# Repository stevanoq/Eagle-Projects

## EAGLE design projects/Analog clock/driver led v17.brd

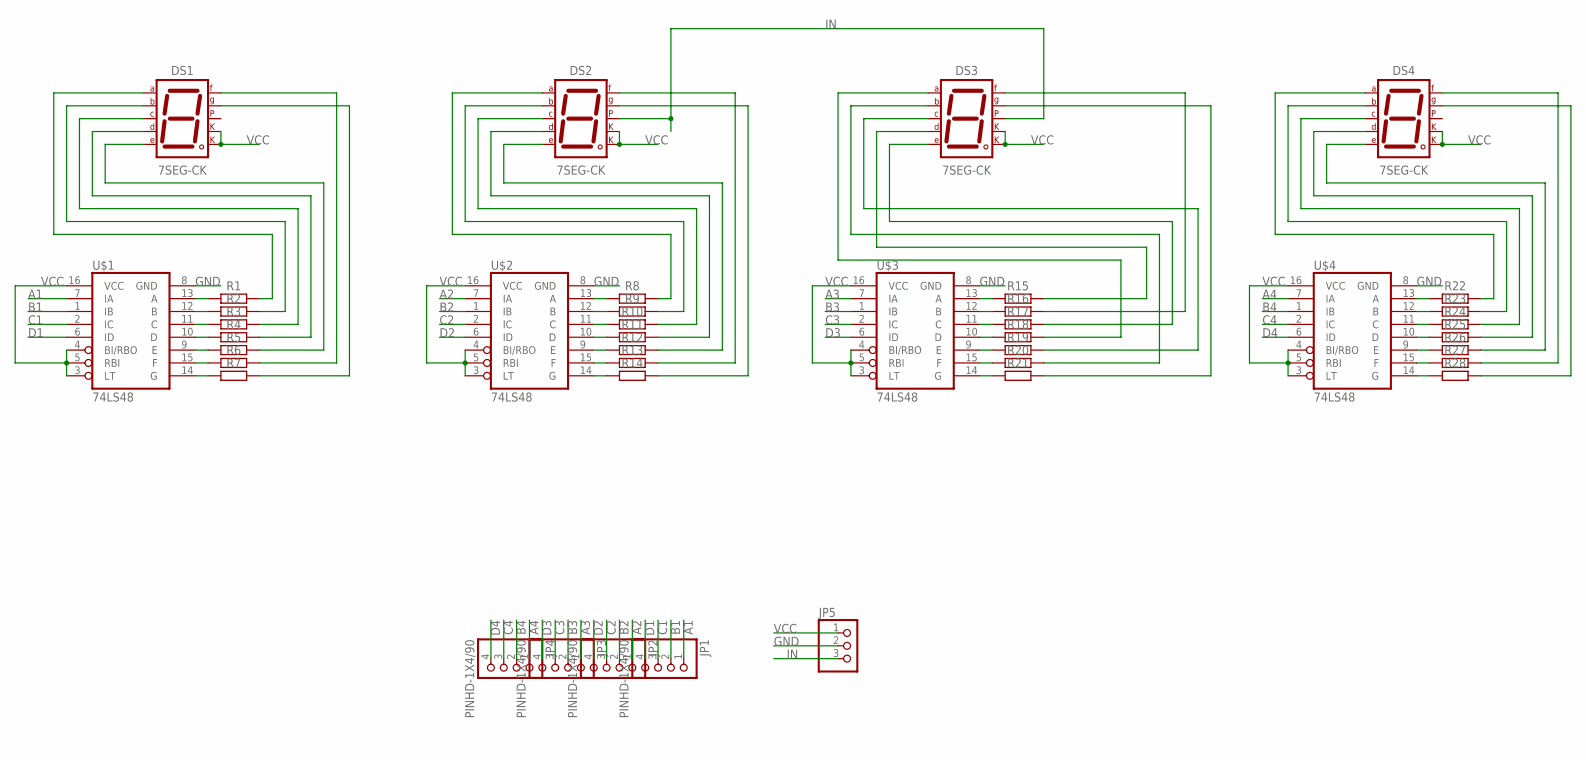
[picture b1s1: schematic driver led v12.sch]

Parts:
DS1, DS2, DS3, DS4: 7SEG-CK; 7SEG-13
JP1, JP2, JP3, JP4: PINHD-1X4/90; 1X04/90
JP5: PINHD-1X3CB; 1X03-CLEANBIG
R1, R2, R3, R4, R5, R6, R7, R8, R9, R10, R11, R12, R13, R14, R15, R16, R17, R18, R19, R20, R21, R22, R23, R24, R25, R26, R27, R28: R_AXIAL-7.2MM-PITCH; RESAD724W46L381D178B
U$1, U$2, U$3, U$4: 74LS48; DIO16

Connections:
A1: JP1.1, U$1.7 (IA)
A2: JP2.1, U$2.7 (IA)
A3: JP3.1, U$3.7 (IA)
A4: JP4.1, U$4.7 (IA)
B1: JP1.2, U$1.1 (IB)
B2: JP2.2, U$2.1 (IB)
B3: JP3.2, U$3.1 (IB)
B4: JP4.2, U$4.1 (IB)
C1: JP1.3, U$1.2 (IC)
C2: JP2.3, U$2.2 (IC)
C3: JP3.3, U$3.2 (IC)
C4: JP4.3, U$4.2 (IC)
D1: JP1.4, U$1.6 (ID)
D2: JP2.4, U$2.6 (ID)
D3: JP3.4, U$3.6 (ID)
D4: JP4.4, U$4.6 (ID)
GND: JP5.2, U$1.8 (GND), U$2.8 (GND), U$3.8 (GND), U$4.8 (GND)
IN: DS2.5 (DP), DS3.5 (DP), JP5.3
unnamed: DS1.7 (A), R1.2
unnamed: DS1.6 (B), R2.2
unnamed: DS1.4 (C), R3.2
unnamed: DS1.2 (D), R4.2
unnamed: DS1.1 (E), R5.2
unnamed: R1.1, U$1.13 (A)
unnamed: R2.1, U$1.12 (B)
unnamed: DS2.7 (A), R8.2
unnamed: DS2.6 (B), R9.2
unnamed: R3.1, U$1.11 (C)
unnamed: R4.1, U$1.10 (D)
unnamed: R5.1, U$1.9 (E)
unnamed: DS1.9 (F), R6.2
unnamed: DS1.10 (G), R7.2
unnamed: R6.1, U$1.15 (F)
unnamed: R7.1, U$1.14 (G)
unnamed: DS2.4 (C), R10.2
unnamed: DS2.2 (D), R11.2
unnamed: DS2.1 (E), R12.2
unnamed: DS2.9 (F), R13.2
unnamed: DS2.10 (G), R14.2
unnamed: R8.1, U$2.13 (A)
unnamed: R9.1, U$2.12 (B)
unnamed: R10.1, U$2.11 (C)
unnamed: R11.1, U$2.10 (D)
unnamed: R12.1, U$2.9 (E)
unnamed: R13.1, U$2.15 (F)
unnamed: R14.1, U$2.14 (G)
unnamed: DS3.7 (A), R18.2
unnamed: DS3.6 (B), R20.2
unnamed: DS3.9 (F), R16.2
unnamed: R15.1, U$3.13 (A)
unnamed: R16.1, U$3.12 (B)
unnamed: R17.1, U$3.11 (C)
unnamed: R18.1, U$3.10 (D)
unnamed: R19.1, U$3.9 (E)
unnamed: R20.1, U$3.15 (F)
unnamed: R21.1, U$3.14 (G)
unnamed: DS4.7 (A), R22.2
unnamed: DS4.6 (B), R23.2
unnamed: DS4.4 (C), R24.2
unnamed: DS4.2 (D), R25.2
unnamed: DS4.1 (E), R26.2
unnamed: DS4.9 (F), R27.2
unnamed: DS4.10 (G), R28.2
unnamed: R22.1, U$4.13 (A)
unnamed: R23.1, U$4.12 (B)
unnamed: R24.1, U$4.11 (C)
unnamed: R25.1, U$4.10 (D)
unnamed: R26.1, U$4.9 (E)
unnamed: R27.1, U$4.15 (F)
unnamed: R28.1, U$4.14 (G)
unnamed: DS3.1 (E), R17.2
unnamed: DS3.2 (D), R15.2
unnamed: DS3.4 (C), R19.2
unnamed: DS3.10 (G), R21.2
VCC: DS1.3 (CK1), DS1.8 (CK2), DS2.3 (CK1), DS2.8 (CK2), DS3.3 (CK1), DS3.8 (CK2), DS4.3 (CK1), DS4.8 (CK2), JP5.1, U$1.3 (LT), U$1.4 (BI/RBO), U$1.5 (RBI), U$1.16 (VCC), U$2.3 (LT), U$2.4 (BI/RBO), U$2.5 (RBI), U$2.16 (VCC), U$3.3 (LT), U$3.4 (BI/RBO), U$3.5 (RBI), U$3.16 (VCC), U$4.3 (LT), U$4.4 (BI/RBO), U$4.5 (RBI), U$4.16 (VCC)

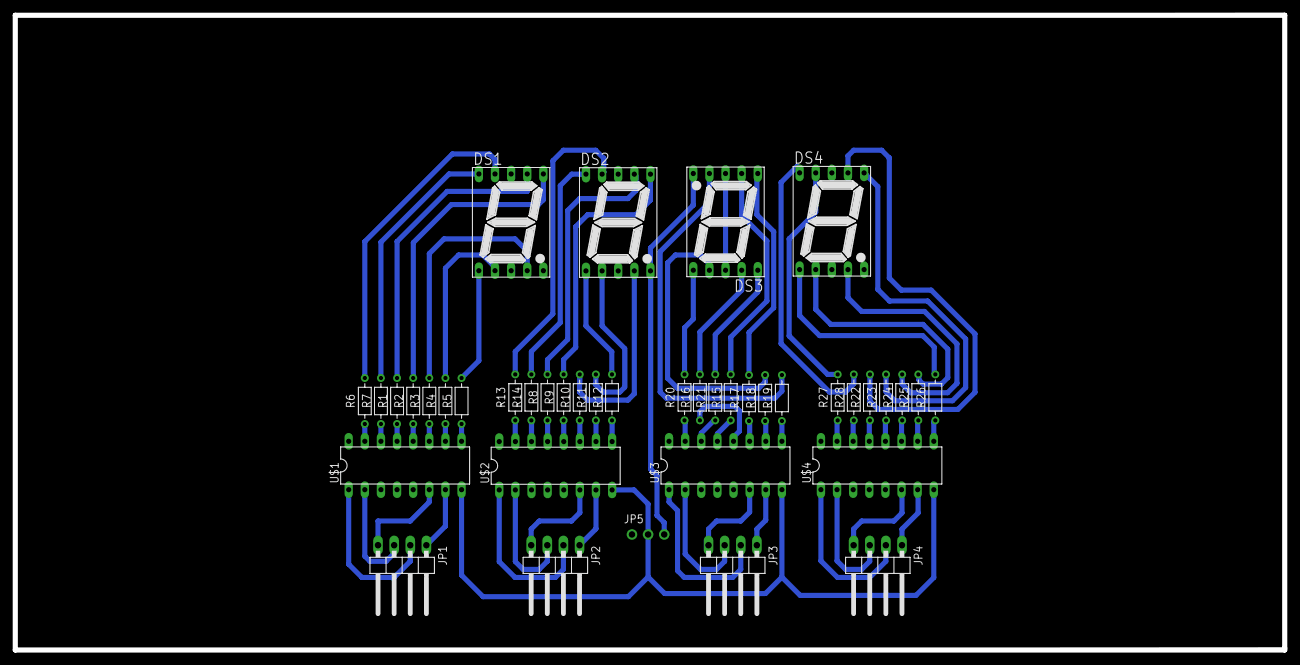
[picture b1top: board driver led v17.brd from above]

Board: 2 copper layers, 200.0 x 100.3 mm, 41 parts (0 on the bottom side), 75 nets.

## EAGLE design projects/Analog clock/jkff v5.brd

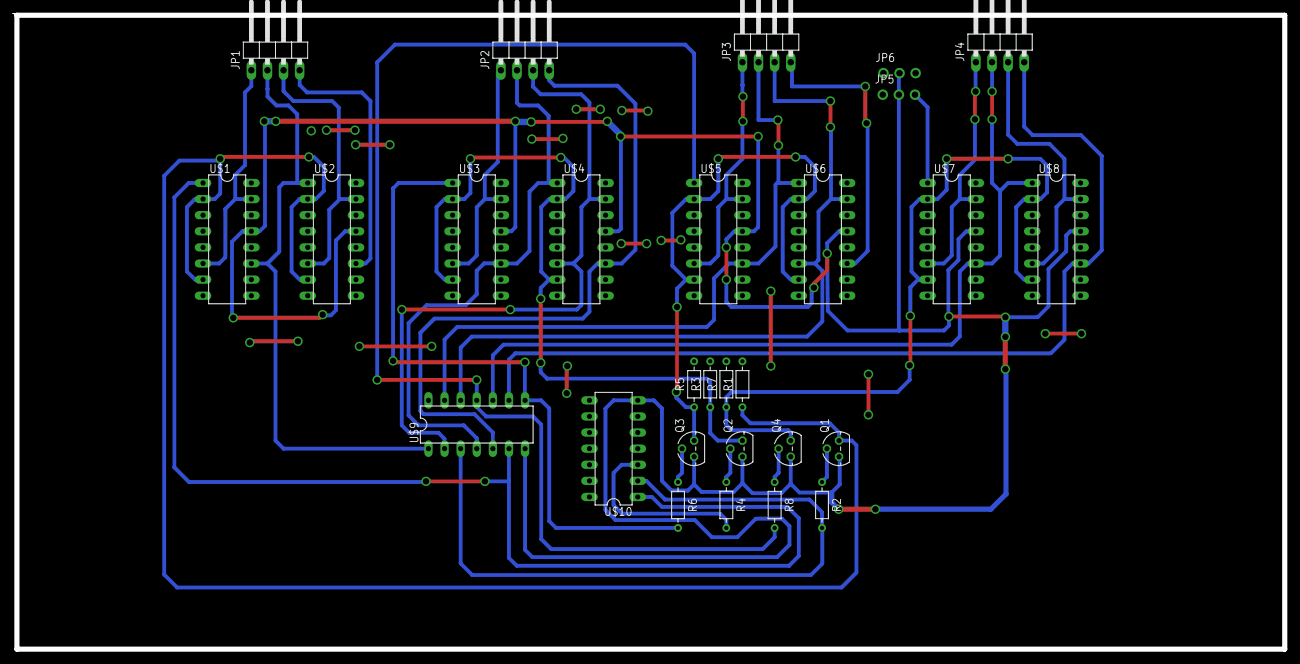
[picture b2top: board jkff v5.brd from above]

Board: 2 copper layers, 200.7 x 100.3 mm, 28 parts (0 on the bottom side), 32 nets.

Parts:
JP1, JP2, JP3, JP4: PINHD-1X4/90; 1X04/90
JP5, JP6: 1X03-CLEANBIG
Q1, Q2, Q3, Q4: NPN; TO92
R1, R2, R3, R4, R5, R6, R7, R8: RESAD724W46L381D178B
U$1, U$2, U$3, U$4, U$5, U$6, U$7, U$8: 74LS76; DIO16
U$9: 74LS08; DIO14
U$10: 74LS32; DIO14

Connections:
A1: JP1.1, U$1.6, U$1.15
A2: JP2.1, U$3.6, U$3.15
A3: JP3.1, U$5.6, U$5.15
A4: JP4.1, U$7.6, U$7.15
B1: JP1.2, U$1.11, U$2.1, U$9.1
B2: JP2.2, U$3.11, U$4.1, U$9.4
B3: JP3.2, U$5.11, U$6.1, U$9.13
B4: JP4.2, U$7.11, U$8.1, U$9.10
C1: JP1.3, U$2.6, U$2.15
C2: JP2.3, U$4.6, U$4.15, U$9.2
C3: JP3.3, U$6.6, U$6.15, U$9.12
C4: JP4.3, U$8.6, U$8.15
D1: JP1.4, U$2.11
D2: JP2.4, U$4.11, U$9.5
D3: JP3.4, U$6.11
D4: JP4.4, U$8.11, U$9.9
GND: JP5.2, JP6.2, Q1.1, Q2.1, Q3.1, Q4.1, U$1.13, U$2.13, U$3.13, U$4.13, U$5.13, U$6.13, U$7.13, U$8.13, U$9.7, U$10.7
IN: JP5.3, U$7.1
unnamed: Q2.2, R4.1
unnamed: Q3.2, R6.1
unnamed: Q4.2, R8.1
unnamed: Q1.2, R2.1
OUT1: R2.2, U$9.3, U$10.2
OUT2: U$1.1, U$9.6, U$10.1
OUT3: R6.2, U$3.1, U$9.8
OUT4: R8.2, U$5.1, U$9.11
OUT32: R4.2, U$10.3
RES1: Q1.3, R1.1, U$1.2, U$1.7, U$2.2, U$2.7
RES2: Q2.3, R3.1, U$3.2, U$3.7, U$4.2, U$4.7
RES3: Q3.3, R5.1, U$5.2, U$5.7, U$6.2, U$6.7
RES4: Q4.3, R7.1, U$7.2, U$7.7, U$8.2, U$8.7
VCC: JP5.1, JP6.1, R1.2, R3.2, R5.2, R7.2, U$1.4, U$1.5, U$1.9, U$1.12, U$1.16, U$2.4, U$2.5, U$2.9, U$2.12, U$2.16, U$3.4, U$3.5, U$3.9, U$3.12, U$3.16, U$4.4, U$4.5, U$4.9, U$4.12, U$4.16, U$5.4, U$5.5, U$5.9, U$5.12, U$5.16, U$6.4, U$6.5, U$6.9, U$6.12, U$6.16, U$7.4, U$7.5, U$7.9, U$7.12, U$7.16, U$8.4, U$8.5, U$8.9, U$8.12, U$8.16, U$9.14, U$10.14

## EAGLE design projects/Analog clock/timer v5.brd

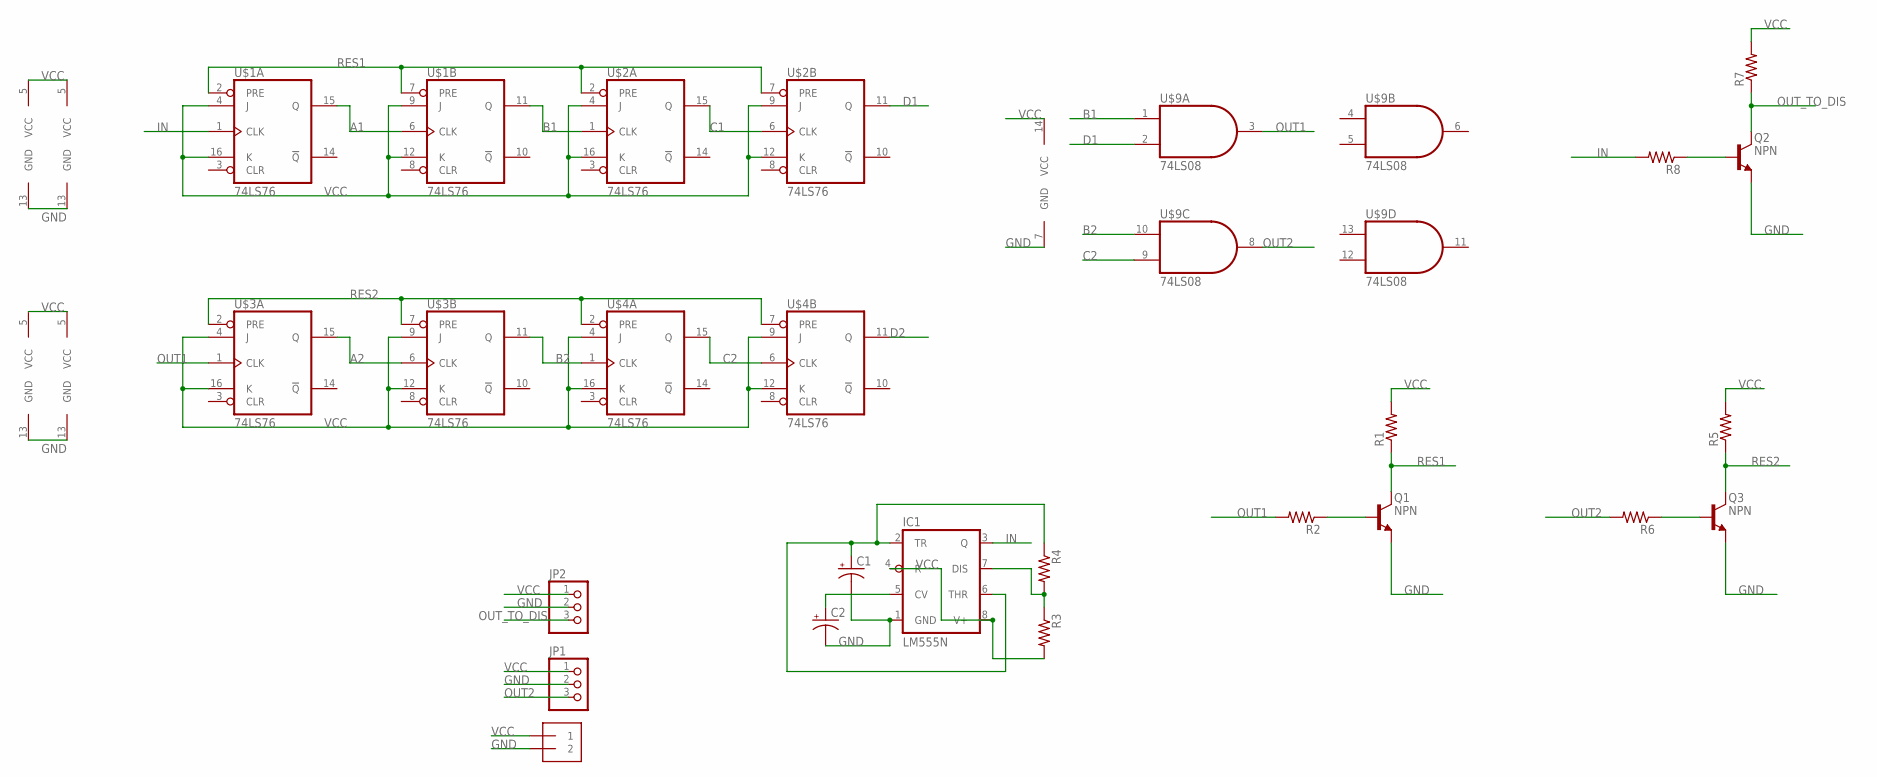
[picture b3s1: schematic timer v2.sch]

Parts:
C1, C2: C-POL-US_RADIAL-20MM-DIA; CAPPRD550W60D1200H2000B
IC1: LM555N; DIL08-ROUND
J1: 1X2-3.5MM
JP1, JP2: PINHD-1X3CB; 1X03-CLEANBIG
Q1, Q2, Q3: NPN; TO92
R1, R2, R3, R4, R5, R6, R7, R8: R-US_AXIAL-7.2MM-PITCH; RESAD724W46L381D178B
U$1, U$2, U$3, U$4: 74LS76; DIO16
U$9: 74LS08; DIO14

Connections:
A1: U$1.6 (CLK), U$1.15 (Q)
A2: U$3.6 (CLK), U$3.15 (Q)
B1: U$1.11 (Q), U$2.1 (CLK), U$9.1 (I0)
B2: U$3.11 (Q), U$4.1 (CLK), U$9.10 (I0)
C1: U$2.6 (CLK), U$2.15 (Q)
C2: U$4.6 (CLK), U$4.15 (Q), U$9.9 (I1)
D1: U$2.11 (Q), U$9.2 (I1)
D2: U$4.11 (Q)
GND: C1.2 (-), C2.2 (-), IC1.1 (GND), J1.2, JP1.2, JP2.2, Q1.1 (E), Q2.1 (E), Q3.1 (E), U$1.13 (GND), U$2.13 (GND), U$3.13 (GND), U$4.13 (GND), U$9.7 (GND)
IN: IC1.3 (Q), R8.2, U$1.1 (CLK)
unnamed: IC1.7 (DIS), R3.1, R4.2
unnamed: C1.1 (+), IC1.2 (TR), IC1.6 (THR), R4.1
unnamed: C2.1 (+), IC1.5 (CV)
unnamed: Q2.2 (B), R8.1
unnamed: Q3.2 (B), R6.1
unnamed: Q1.2 (B), R2.1
OUT1: R2.2, U$3.1 (CLK), U$9.3 (O)
OUT2: JP1.3, R6.2, U$9.8 (O)
OUT_TO_DIS: JP2.3, Q2.3 (C), R7.1
RES1: Q1.3 (C), R1.1, U$1.2 (PRE), U$1.7 (PRE), U$2.2 (PRE), U$2.7 (PRE)
RES2: Q3.3 (C), R5.1, U$3.2 (PRE), U$3.7 (PRE), U$4.2 (PRE), U$4.7 (PRE)
VCC: IC1.4 (R), IC1.8 (V+), J1.1, JP1.1, JP2.1, R1.2, R3.2, R5.2, R7.2, U$1.4 (J), U$1.5 (VCC), U$1.9 (J), U$1.12 (K), U$1.16 (K), U$2.4 (J), U$2.5 (VCC), U$2.9 (J), U$2.12 (K), U$2.16 (K), U$3.4 (J), U$3.5 (VCC), U$3.9 (J), U$3.12 (K), U$3.16 (K), U$4.4 (J), U$4.5 (VCC), U$4.9 (J), U$4.12 (K), U$4.16 (K), U$9.14 (VCC)

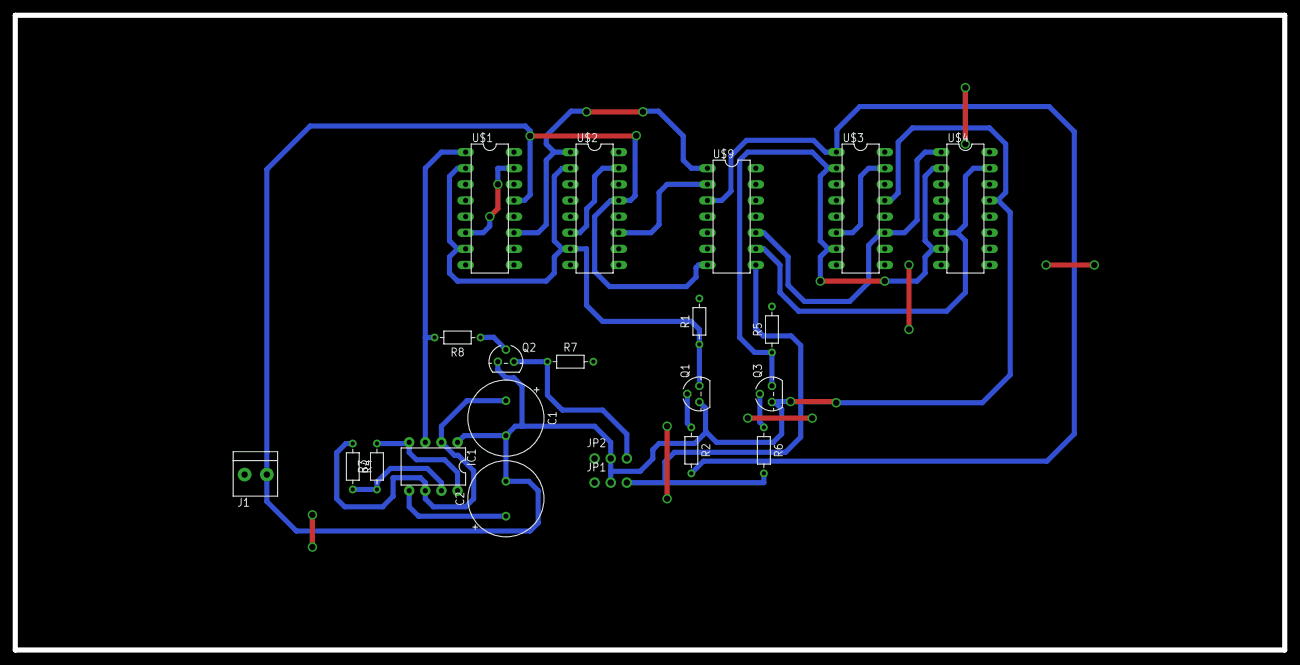
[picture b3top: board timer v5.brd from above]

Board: 2 copper layers, 200.0 x 100.0 mm, 22 parts (0 on the bottom side), 21 nets.

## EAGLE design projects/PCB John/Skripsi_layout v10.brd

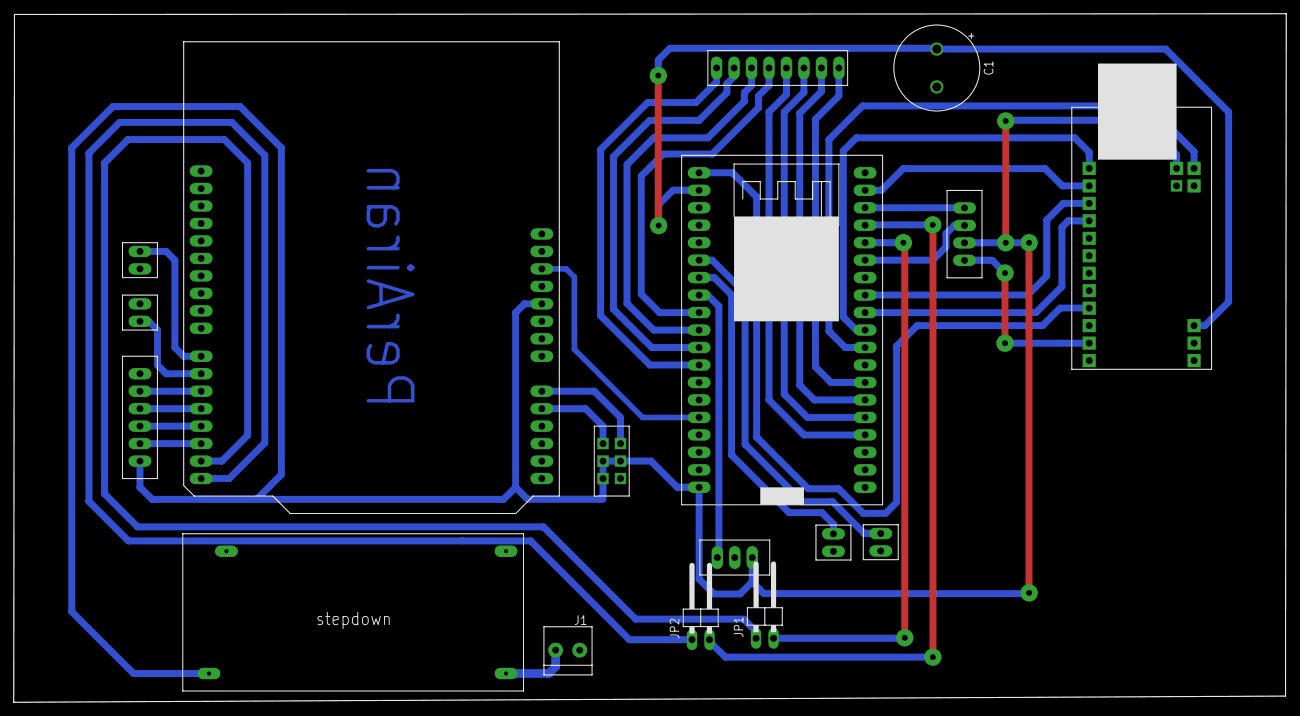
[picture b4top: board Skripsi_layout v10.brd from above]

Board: 2 copper layers, 185.0 x 100.1 mm, 17 parts (0 on the bottom side), 36 nets.

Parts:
C1: CAPPRD550W110D1250H2500B
J1: 1X2-3.5MM
JP1, JP2: PINHD-1X2/90; 1X02/90
U$1: ARDUINO_UNO
U$2: ESP32_NEW
U$3: USB_HOST
U$4: LCD_I2C
U$5: KEYPAD_4X4
U$6: IR_SENSOR
U$7, U$8, U$11, U$12: SWITCHLIMITER; SWICHLIMITER
U$9: RELAY_4CHANNEL
U$10: MOTOR_DRIVER_BTS7960
U$13: XL4005E1

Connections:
3V3: U$2.3V3, U$3.3V3
5V: U$1.5V, U$2.5V, U$3.VBUS, U$4.VCC, U$6.VCC, U$9.VCC, U$10.LEN, U$10.REN, U$10.VCC, U$13.OUTT+
GND: C1.2, J1.1, U$1.GND, U$2.GND, U$3.GND, U$4.GND, U$6.GND, U$7.COM, U$8.COM, U$9.GND, U$10.GND, U$11.COM, U$12.COM, U$13.IN-, U$13.OUT-
unnamed: U$2.4, U$5.R1
unnamed: U$2.17, U$3.INT
unnamed: C1.1, U$2.EN, U$3.RST
unnamed: U$2.SS, U$3.SS
unnamed: U$2.SCK, U$3.SCK
unnamed: U$2.MISO, U$3.MISO
unnamed: U$2.MOSI, U$3.MOSI
unnamed: U$2.0, U$5.R2
unnamed: U$2.2, U$5.R3
unnamed: U$2.15, U$5.R4
unnamed: U$2.25, U$5.C1
unnamed: U$1.D2, U$9.IN4
unnamed: U$1.D3, U$9.IN3
unnamed: U$2.26, U$5.C2
unnamed: U$2.27, U$5.C3
unnamed: U$2.14, U$5.C4
unnamed: U$1.D4, U$9.IN2
unnamed: U$2.32, U$8.NO
unnamed: U$2.33, U$6.OUT
unnamed: U$2.35, U$7.NO
unnamed: U$1.D5, U$9.IN1
unnamed: U$1.D6, U$12.NO
unnamed: U$1.A0, U$10.LPWM
unnamed: U$1.A1, U$10.RPWM
unnamed: U$1.D7, U$11.NO
unnamed: J1.2, U$13.IN+
unnamed: U$1.RESET, U$2.13
RX: JP1.2, U$2.RX
RXA: JP2.1, U$1.D0
SCL: U$2.SCL, U$4.SCL
SDA: U$2.SDA, U$4.SDA
TX: JP2.2, U$2.TX
TXA: JP1.1, U$1.D1

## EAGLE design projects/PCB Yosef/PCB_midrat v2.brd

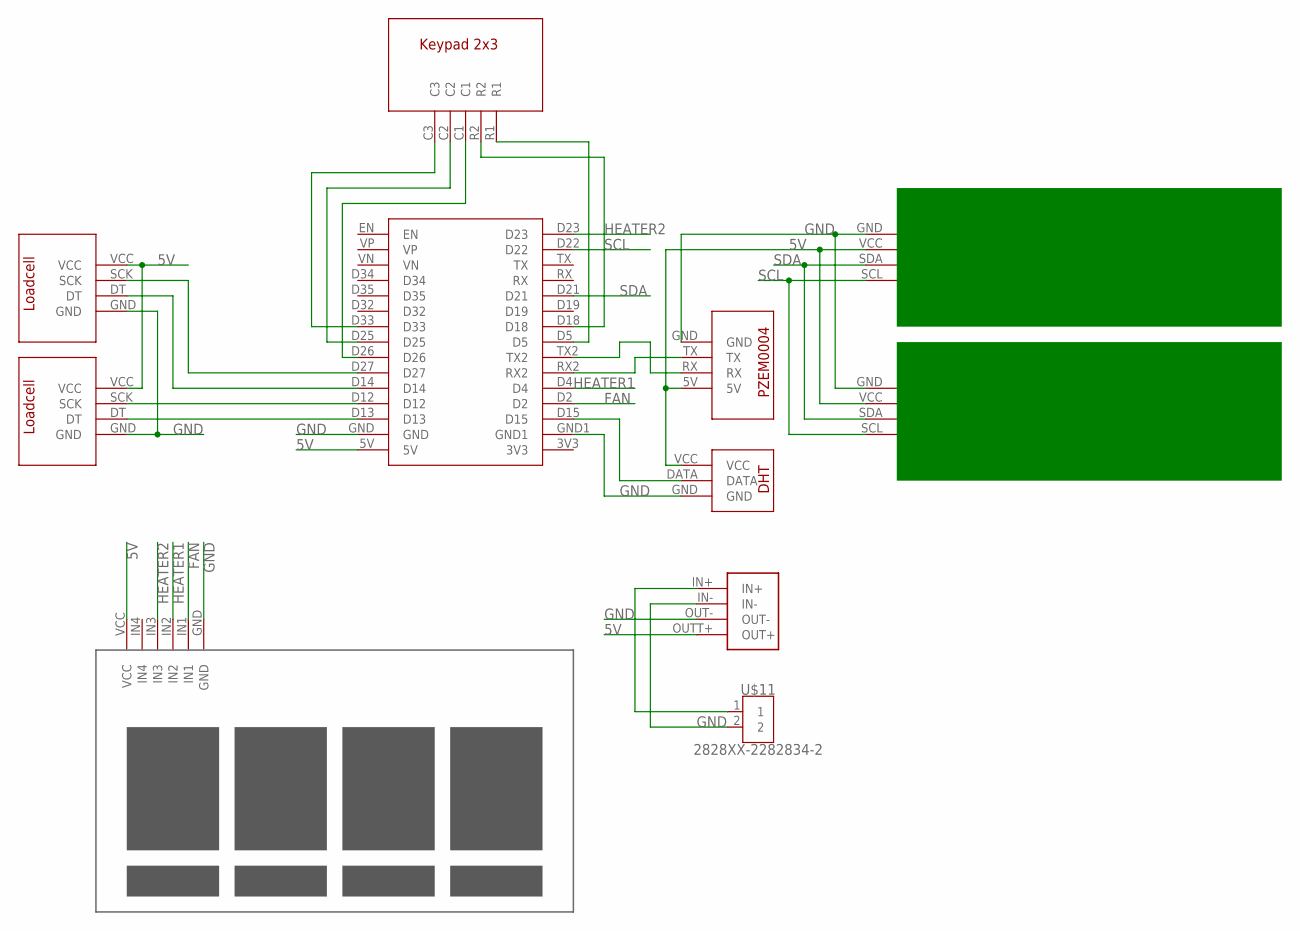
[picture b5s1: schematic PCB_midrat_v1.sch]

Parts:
U$1: ESP32_30PIN
U$2: KEYPAD_2X3; KEYPAD2X3
U$3, U$8: LCD_I2C
U$4, U$7: LOADCELL
U$5: PZEM0004
U$6: RELAY_4CHANNEL
U$9: XL4005E1
U$10: DHT
U$11: 2828XX-2282834-2; TERMBLK_254-2N

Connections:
5V: U$1.5V, U$3.VCC, U$4.VCC, U$5.5V, U$6.VCC, U$7.VCC, U$8.VCC, U$9.OUTT+ (OUT+), U$10.VCC
FAN: U$1.D2, U$6.IN1
GND: U$1.GND, U$1.GND1, U$3.GND, U$4.GND, U$5.GND, U$6.GND, U$7.GND, U$8.GND, U$9.IN-, U$9.OUT-, U$10.GND, U$11.2
HEATER1: U$1.D4, U$6.IN2
HEATER2: U$1.D23, U$6.IN3
unnamed: U$1.D13, U$4.DT
unnamed: U$1.D12, U$4.SCK
unnamed: U$1.D14, U$7.DT
unnamed: U$1.D27, U$7.SCK
unnamed: U$1.D26, U$2.C1
unnamed: U$1.D25, U$2.C2
unnamed: U$1.D33, U$2.C3
unnamed: U$1.D5, U$2.R1
unnamed: U$1.D18, U$2.R2
unnamed: U$1.RX2, U$5.TX
unnamed: U$1.TX2, U$5.RX
unnamed: U$1.D15, U$10.DATA
unnamed: U$9.IN+, U$11.1
SCL: U$1.D22, U$3.SCL, U$8.SCL
SDA: U$1.D21, U$3.SDA, U$8.SDA

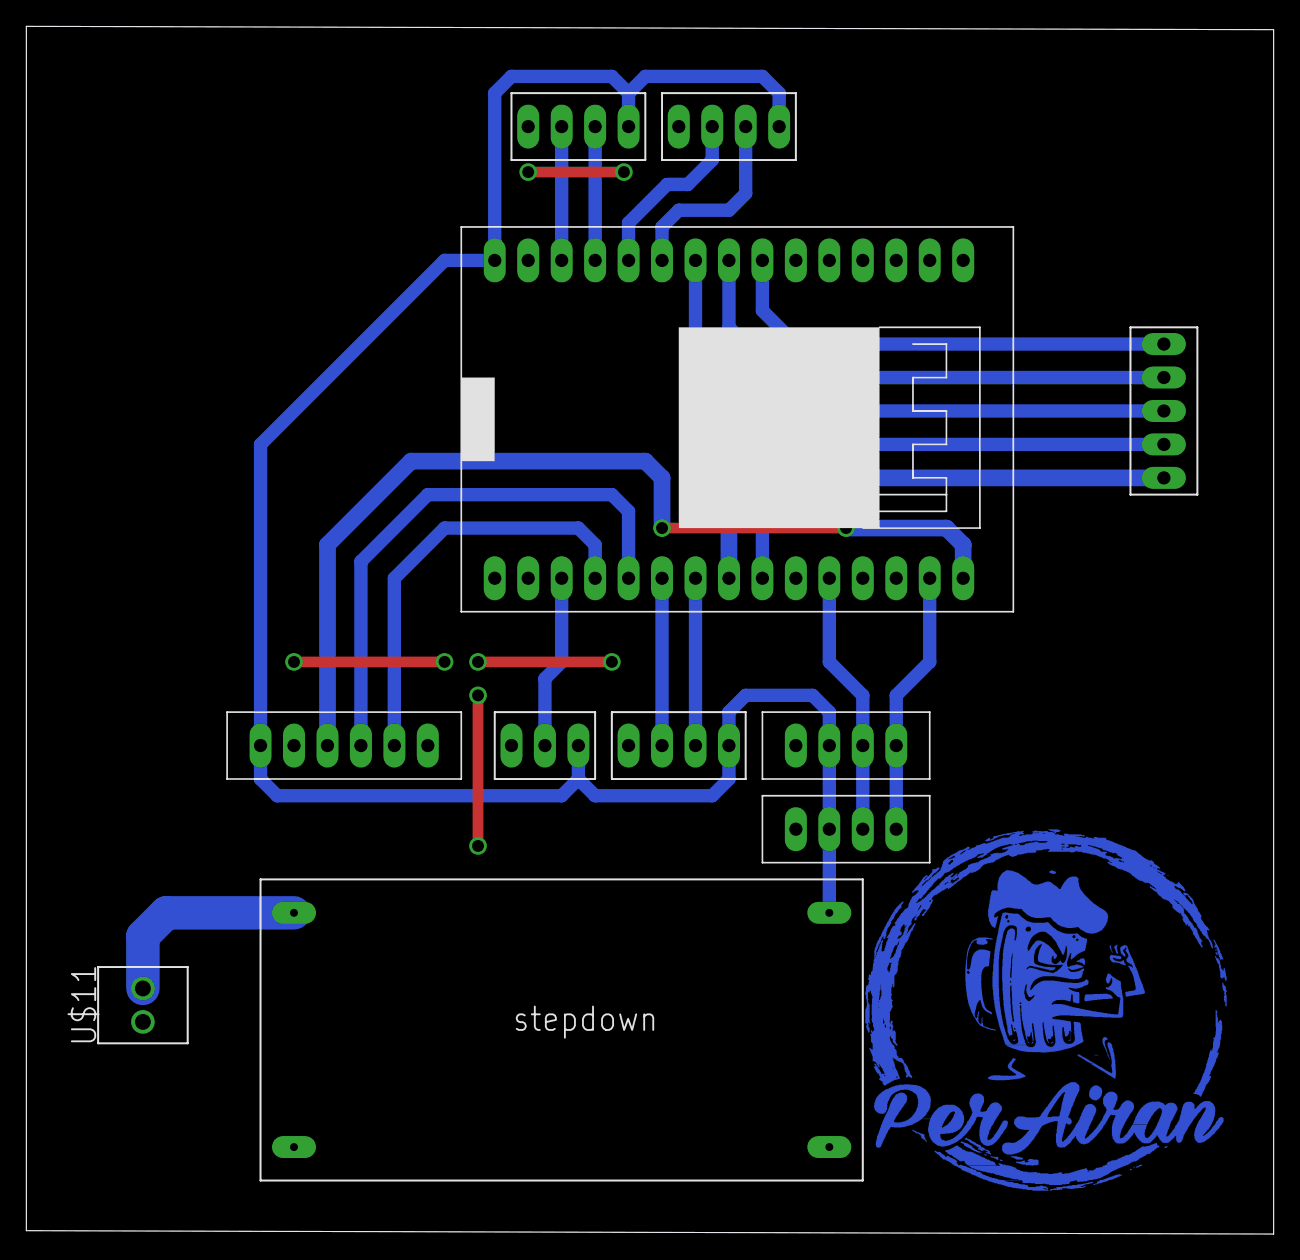
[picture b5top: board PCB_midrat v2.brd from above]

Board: 2 copper layers, 94.7 x 91.7 mm, 11 parts (0 on the bottom side), 20 nets.

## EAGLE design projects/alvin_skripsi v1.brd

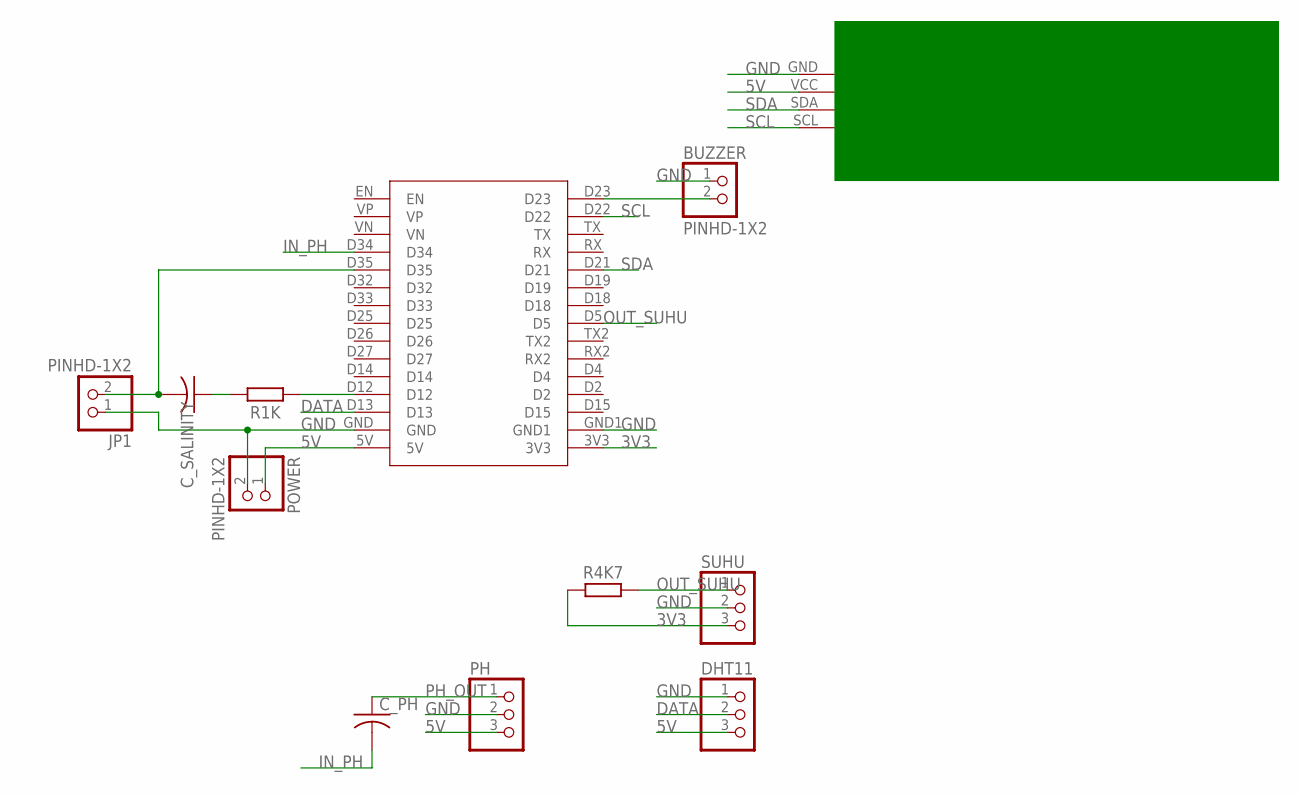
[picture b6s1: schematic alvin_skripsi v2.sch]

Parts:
BUZZER: PINHD-1X2; 1X02
C_PH: C-US_RADIAL-12.5MM-DIA; CAPRD550W60D1025H1250B
C_SALINITY: C-US_RADIAL-12.5MM-DIA; CAPRD550W60D1025H1250B
DHT11: PINHD-1X3CB; 1X03-CLEANBIG
JP1: PINHD-1X2; 1X02
PH: PINHD-1X3CB; 1X03-CLEANBIG
POWER: PINHD-1X2; 1X02
R1K, R4K7: R_AXIAL-7.2MM-PITCH; RESAD724W46L381D178B
SUHU: PINHD-1X3CB; 1X03-CLEANBIG
U$1: ESP32_30PIN
U$2: LCD_I2C

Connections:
3V3: R4K7.1, SUHU.3, U$1.3V3
5V: DHT11.3, PH.3, POWER.1, U$1.5V, U$2.VCC
DATA: DHT11.2, U$1.D13
GND: BUZZER.1, DHT11.1, JP1.1, PH.2, POWER.2, SUHU.2, U$1.GND, U$1.GND1, U$2.GND
IN_PH: C_PH.2, U$1.D34
unnamed: R1K.1, U$1.D12
unnamed: C_SALINITY.1, R1K.2
unnamed: C_SALINITY.2, JP1.2, U$1.D35
unnamed: BUZZER.2, U$1.D23
OUT_SUHU: R4K7.2, SUHU.1, U$1.D5
PH_OUT: C_PH.1, PH.1
SCL: U$1.D22, U$2.SCL
SDA: U$1.D21, U$2.SDA

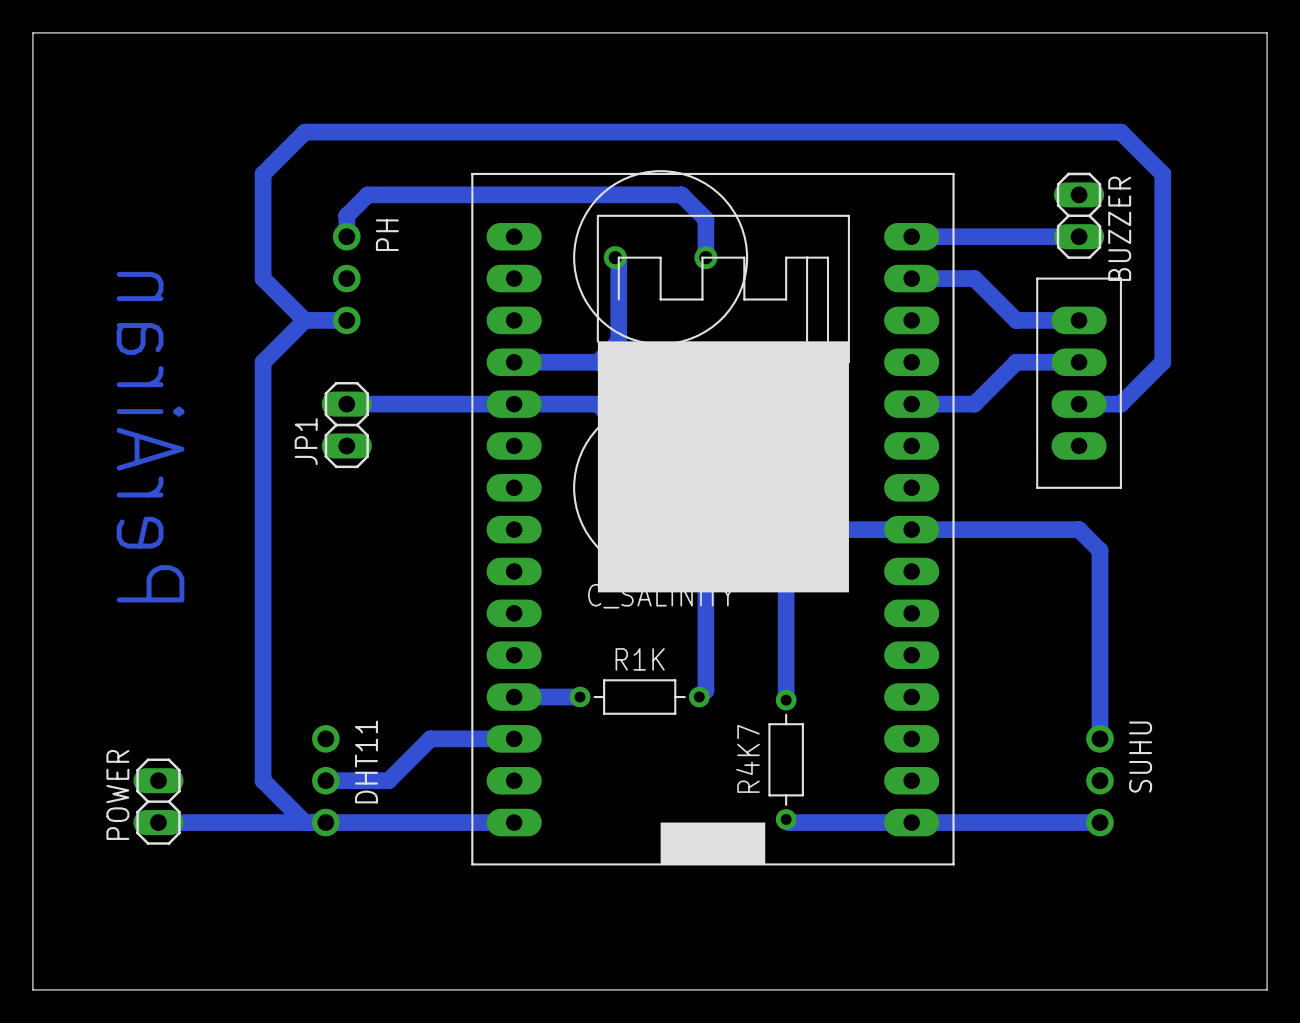
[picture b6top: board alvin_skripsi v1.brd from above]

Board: 2 copper layers, 74.9 x 58.1 mm, 12 parts (0 on the bottom side), 13 nets.

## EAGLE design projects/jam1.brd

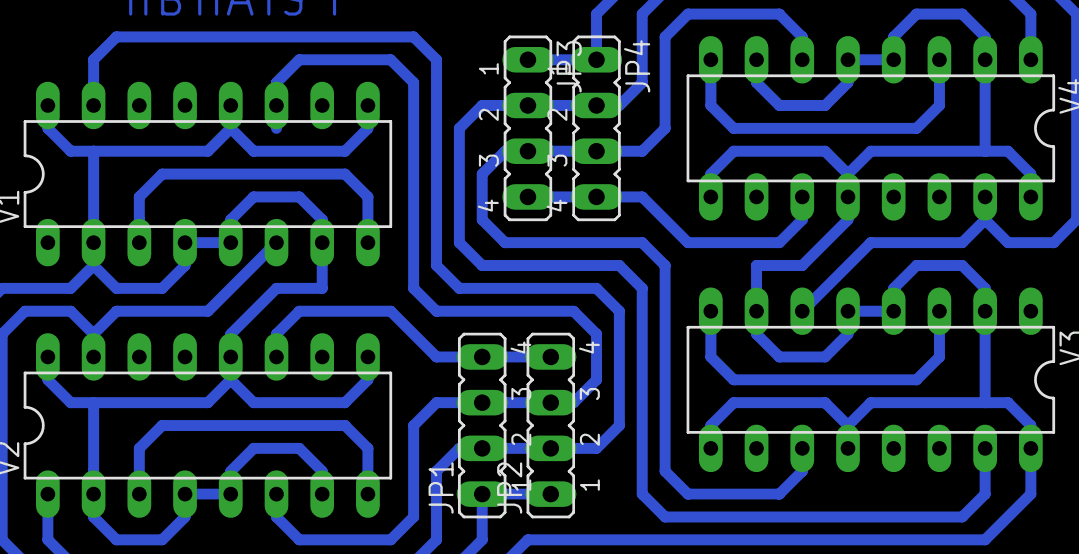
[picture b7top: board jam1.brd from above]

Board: 2 copper layers, 8 parts (0 on the bottom side), 12 nets.

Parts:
JP1, JP2, JP3, JP4: JP4
V1, V2, V3, V4: 7476N; DIL16

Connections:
+UB: V1.2, V1.4, V1.5, V1.7, V1.9, V1.12, V1.16, V2.2, V2.4, V2.5, V2.7, V2.9, V2.12, V2.16, V3.2, V3.4, V3.5, V3.7, V3.9, V3.12, V3.16, V4.2, V4.4, V4.5, V4.7, V4.9, V4.12, V4.16
-UB: V1.13, V2.13, V3.13, V4.13
unnamed: JP1.4, JP2.4, V2.11
unnamed: JP1.3, JP2.3, V1.11, V2.6
unnamed: JP1.1, JP2.1, V1.6, V2.15
unnamed: V3.3, V3.8, V4.3, V4.8
unnamed: JP3.3, JP4.3, V3.11, V4.6
unnamed: JP1.2, JP2.2, V1.15, V2.1
unnamed: JP3.1, JP4.1, V3.6, V4.15
unnamed: V1.3, V1.8, V2.3, V2.8
unnamed: JP3.4, JP4.4, V4.11
unnamed: JP3.2, JP4.2, V3.15, V4.1
